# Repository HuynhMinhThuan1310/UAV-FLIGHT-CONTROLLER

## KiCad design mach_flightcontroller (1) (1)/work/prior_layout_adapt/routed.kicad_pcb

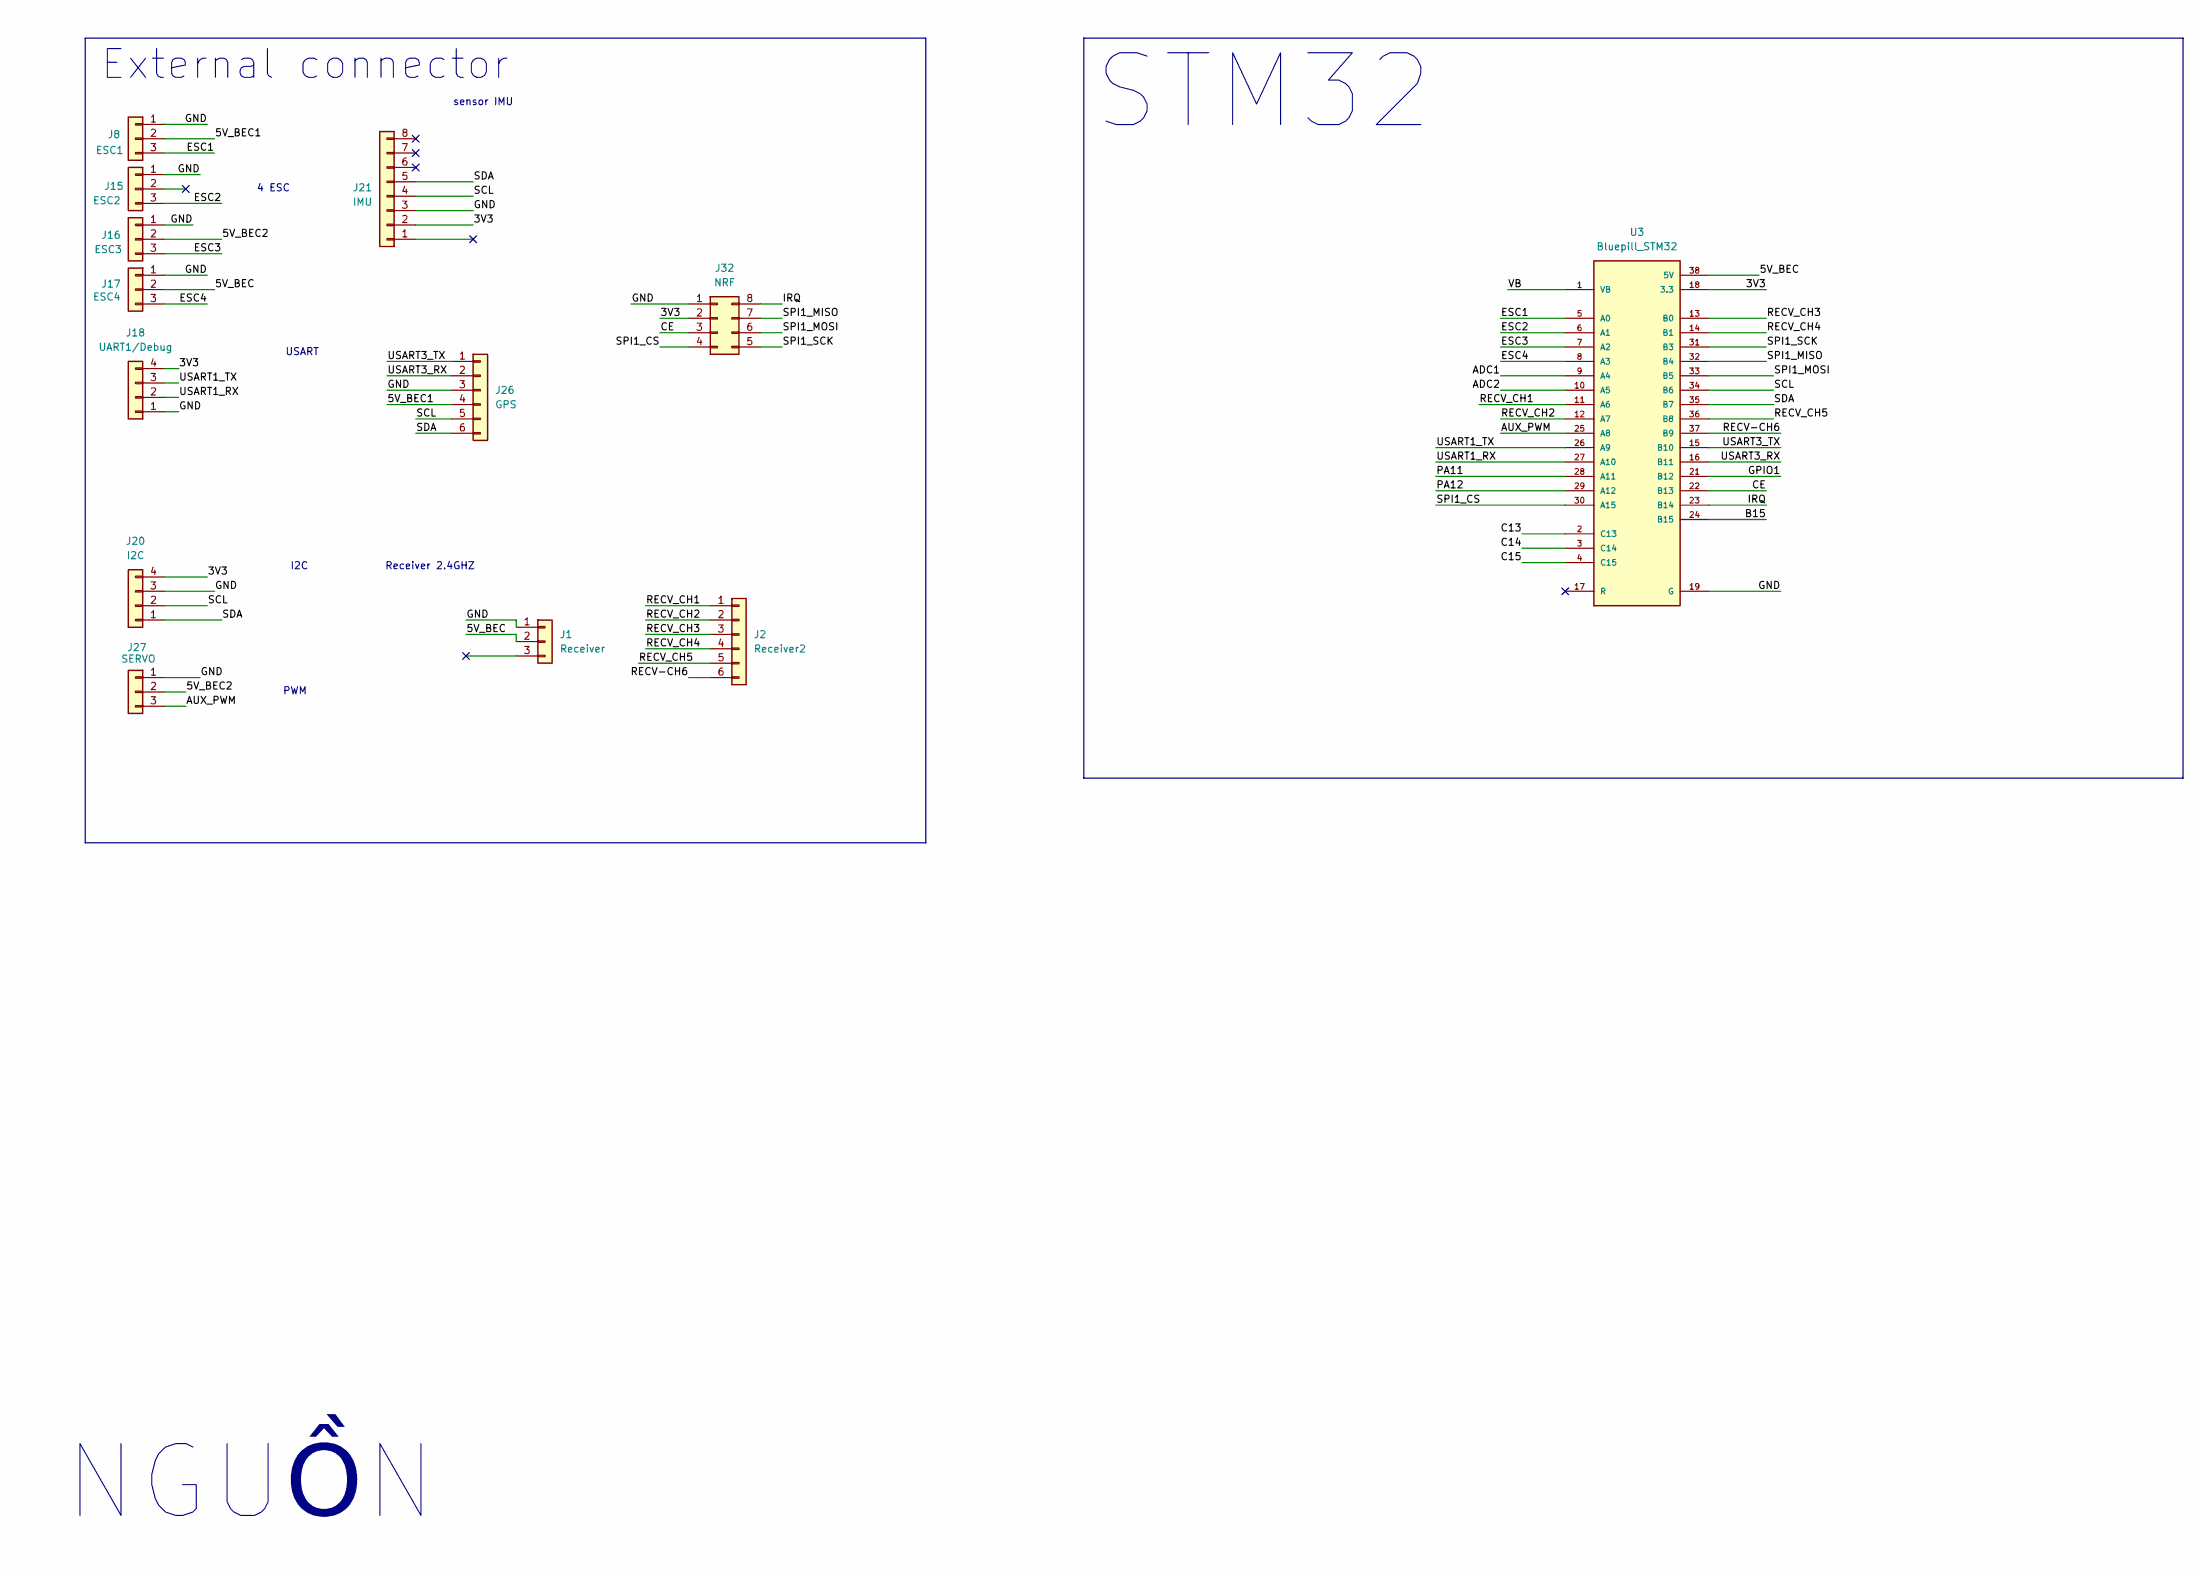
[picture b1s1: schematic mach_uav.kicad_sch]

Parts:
J1: Receiver; PinHeader_1x03_P1.00mm_Vertical
J2: Receiver2; PinHeader_1x06_P1.00mm_Vertical
J8: ESC1; PinHeader_1x03_P1.00mm_Vertical
J15: ESC2; PinHeader_1x03_P1.00mm_Vertical
J16: ESC3; PinHeader_1x03_P1.00mm_Vertical
J17: ESC4; PinHeader_1x03_P1.00mm_Vertical
J18: UART1/Debug; PinHeader_1x04_P1.00mm_Vertical
J20: I2C; PinHeader_1x04_P1.00mm_Vertical
J21: IMU; PinHeader_1x08_P1.00mm_Vertical
J26: GPS; JST_SH_BM06B-SRSS-TB_1x06-1MP_P1.00mm_Vertical
J27: SERVO; PinHeader_1x03_P1.00mm_Vertical
J32: NRF; PinHeader_2x04_P1.00mm_Vertical
U3: Bluepill_STM32; MODULE_ZC323000; PARTREV N/A

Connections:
3.3: J18.4, J20.4, J21.2, J32.2, U3.18 (3.3), U3.40 (3.3)
/5V_BEC: J1.2, J17.2, U3.38 (5V)
/5V_BEC1: J8.2, J26.4
/5V_BEC2: J16.2, J27.2
/ADC1: U3.9 (A4)
/ADC2: U3.10 (A5)
/AUX_PWM: J27.3, U3.25 (A8)
/B15: U3.24 (B15)
/C13: U3.2 (C13)
/C14: U3.3 (C14)
/C15: U3.4 (C15)
/CE: J32.3, U3.22 (B13)
/ESC1: J8.3, U3.5 (A0)
/ESC2: J15.3, U3.6 (A1)
/ESC3: J16.3, U3.7 (A2)
/ESC4: J17.3, U3.8 (A3)
/GPIO1: U3.21 (B12)
/IRQ: J32.8, U3.23 (B14)
/PA11: U3.28 (A11)
/PA12: U3.29 (A12)
/RECV-CH6: J2.6, U3.37 (B9)
/RECV_CH1: J2.1, U3.11 (A6)
/RECV_CH2: J2.2, U3.12 (A7)
/RECV_CH3: J2.3, U3.13 (B0)
/RECV_CH4: J2.4, U3.14 (B1)
/RECV_CH5: J2.5, U3.36 (B8)
/SCL: J20.2, J21.4, J26.5, U3.34 (B6)
/SDA: J20.1, J21.5, J26.6, U3.35 (B7)
/SPI1_CS: J32.4, U3.30 (A15)
/SPI1_MISO: J32.7, U3.32 (B4)
/SPI1_MOSI: J32.6, U3.33 (B5); also elsewhere on the board
/SPI1_SCK: J32.5, U3.31 (B3)
/USART1_RX: J18.2, U3.27 (A10)
/USART1_TX: J18.3, U3.26 (A9)
/USART3_RX: J26.2, U3.16 (B11)
/USART3_TX: J26.1, U3.15 (B10)
/VB: U3.1 (VB)
G: J1.1, J8.1, J15.1, J16.1, J17.1, J18.1, J20.3, J21.3, J26.3, J27.1, J32.1, U3.19 (G), U3.20 (G), U3.39 (G)

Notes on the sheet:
USART
sensor IMU
NGUỒN
External connector
Receiver 2.4GHZ
4 ESC
STM32
I2C
PWM

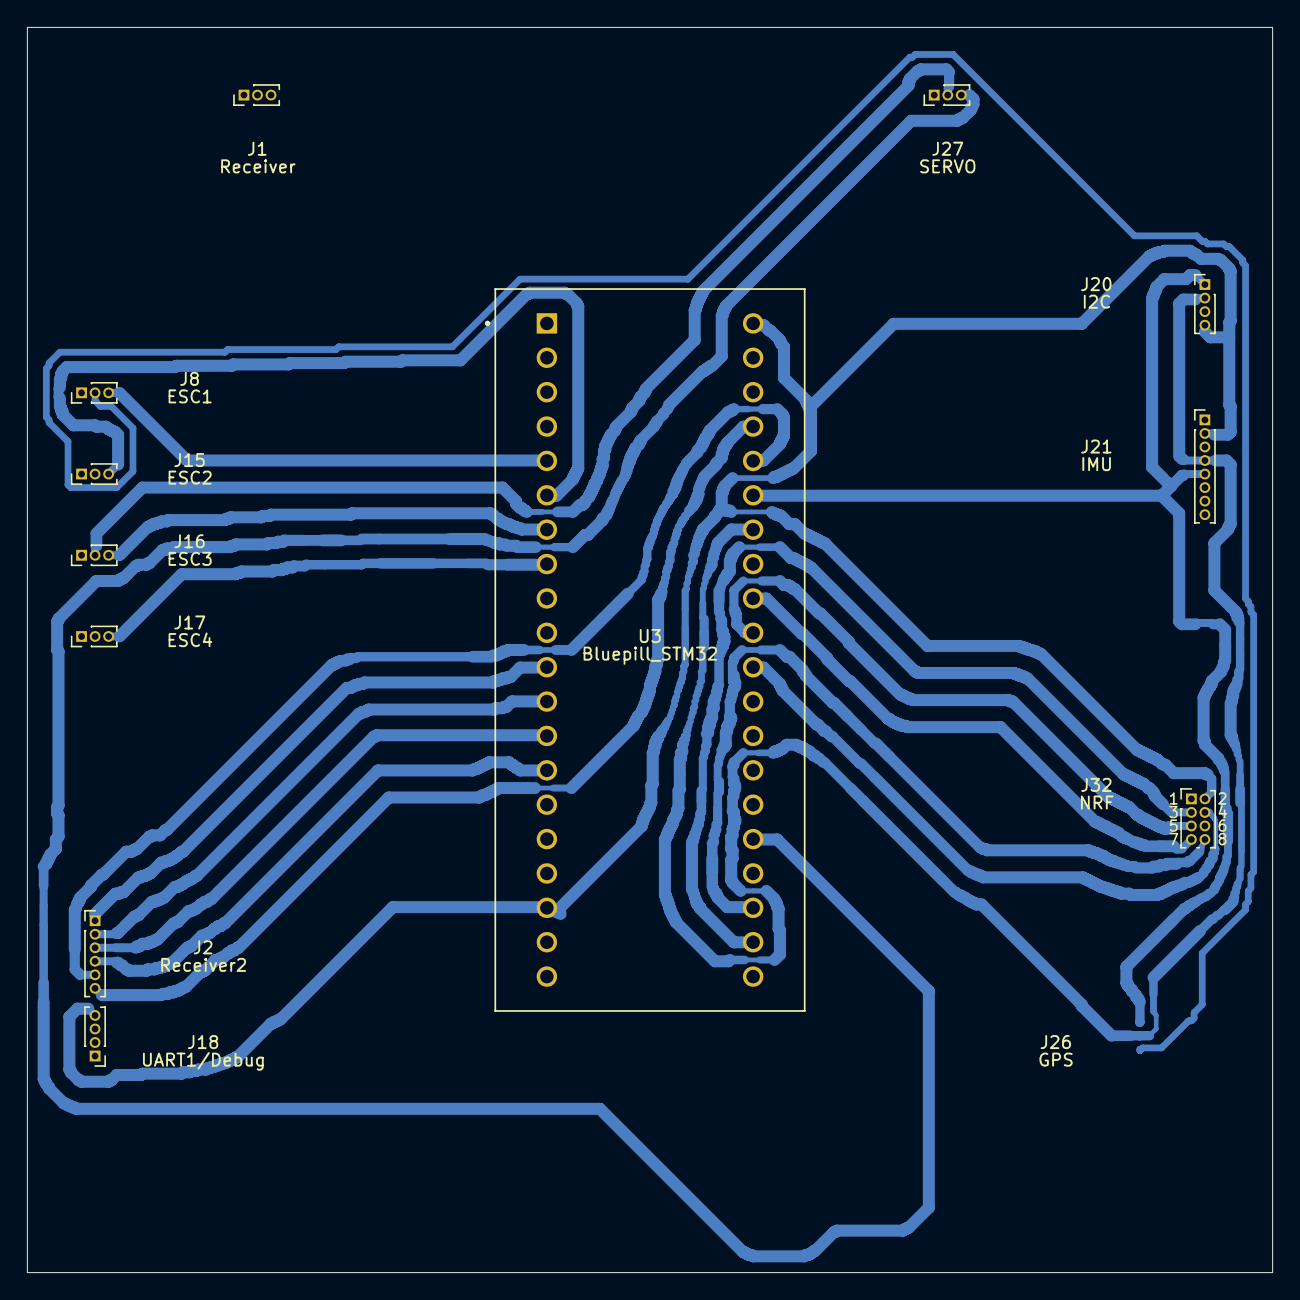
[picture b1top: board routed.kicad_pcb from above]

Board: 2 copper layers, 92.0 x 92.0 mm, 14 parts (1 on the bottom side), 28 nets.

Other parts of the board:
W1: WIRE MOSI; W1_20260923

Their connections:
/SPI1_MOSI: W1.1; also elsewhere on the board
